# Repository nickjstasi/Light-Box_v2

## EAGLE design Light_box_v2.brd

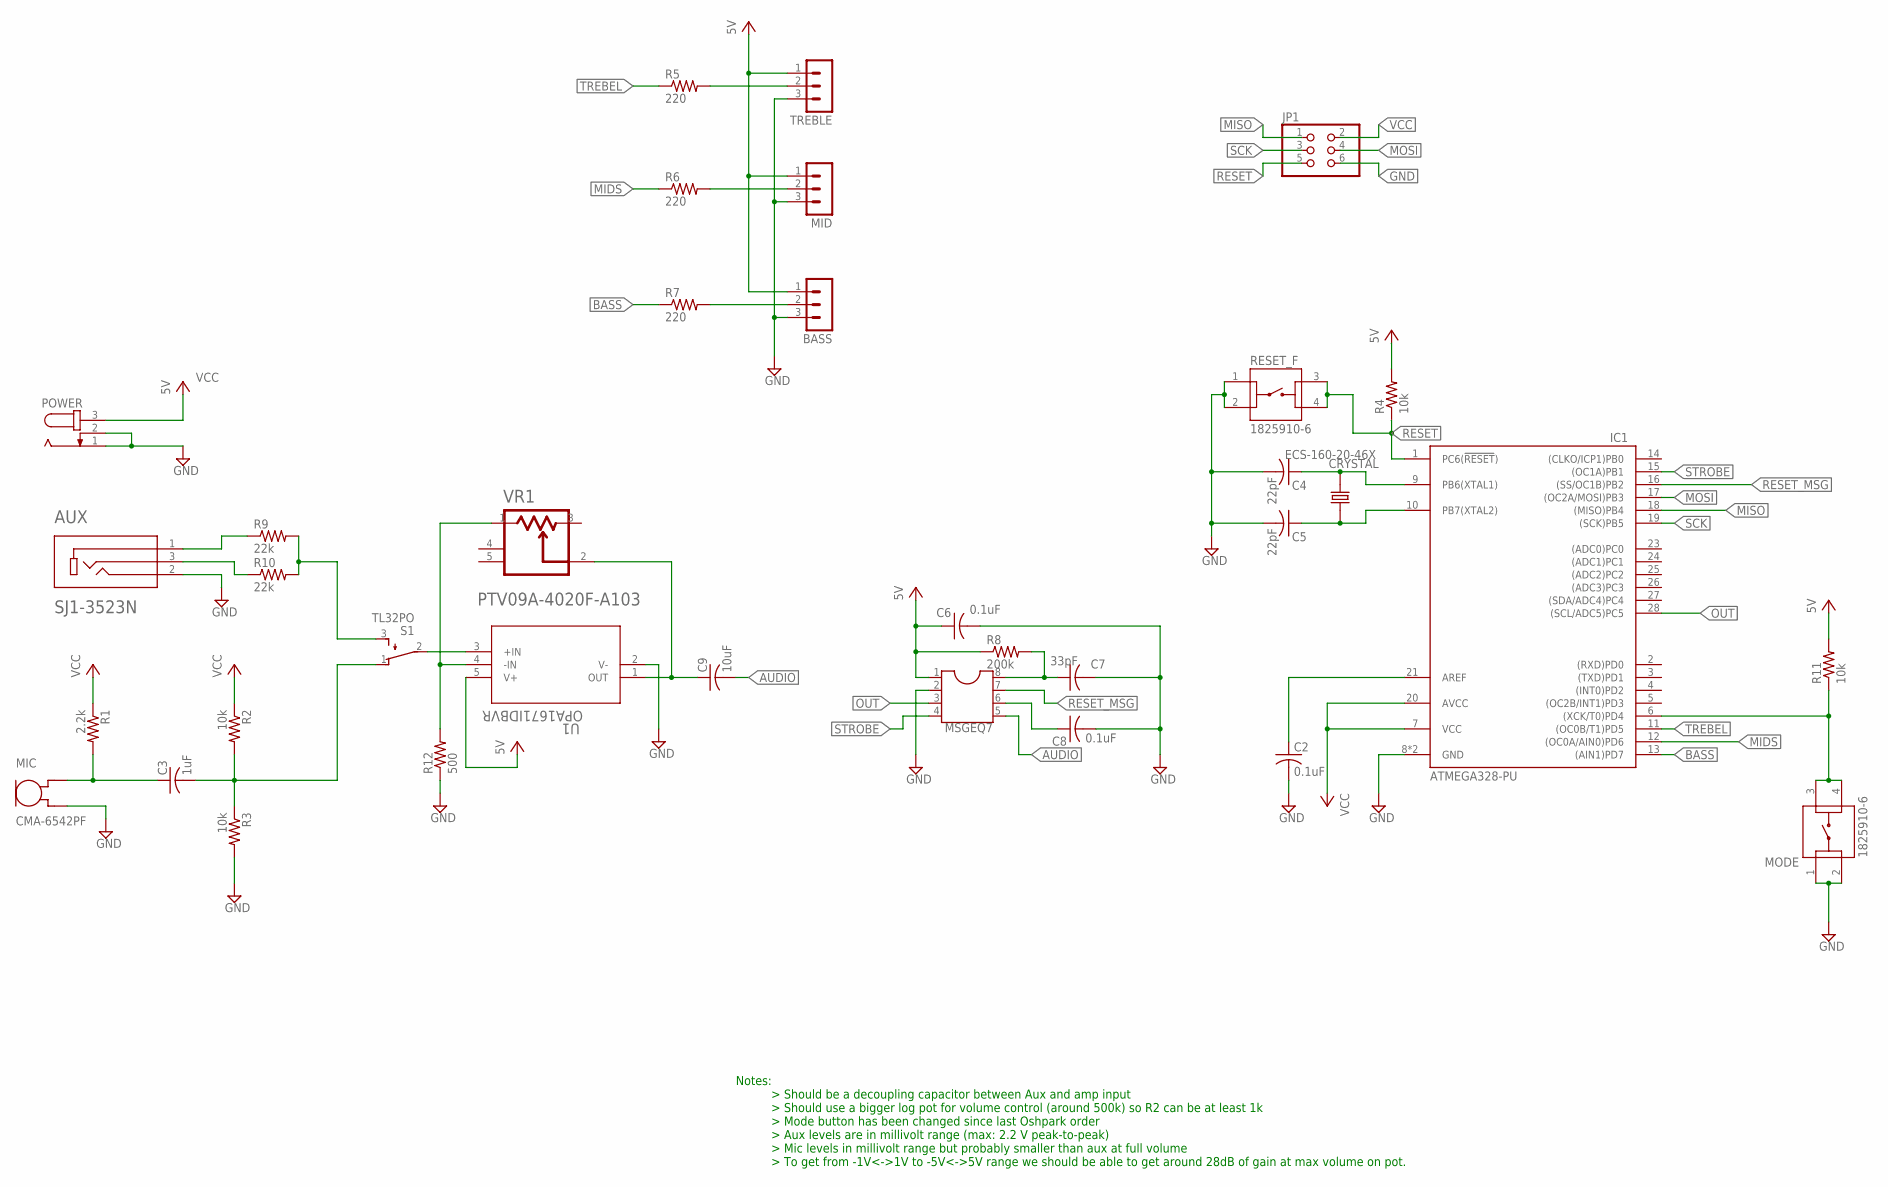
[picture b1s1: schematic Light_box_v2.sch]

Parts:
AUX: SJ1-3523N; CUI_SJ1-3523N
BASS: MA03-1
C2, C6, C8: 0.1uF; C0805
C3: 1uF; C0805
C4, C5: 22pF; C0805
C7: 33pF; C0805
C9: 10uF; C0805
CRYSTAL: ECS-160-20-46X; XTAL_ECS-160-20-46X
IC1: ATMEGA328-PU; DIL28
JP1: PINHD-2X3; 2X03
MIC: CMA-6542PF; CUI_CMA-6542PF
MID: MA03-1
MODE: 1825910-6; SW_1825910-6-4
MSGEQ7: DIL8; DIL08
POWER: JACK-PLUG1; SPC4078
R1: 2.2k; R0805
R2, R3, R4, R11: 10k; R0805
R5, R6, R7: 220; R0805
R8: 200k; R0805
R9, R10: 22k; R0805
R12: 500; R0805
RESET_F: 1825910-6; SW_1825910-6-4
S1: TL32PO; TL3XPO
TREBLE: MA03-1
U1: OPA1671IDBVR; SOT23-DBV5_TEX
VR1: BOURNS_PTV09A-4020F-A103BOURNS_PTV09A-4020F-A103_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; BOURNS_PTV09A-4020F-A103_0

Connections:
AUDIO: C9.2, MSGEQ7.5
BASS: IC1.13 ((AIN1)PD7), R7.1
GND: AUX.2, BASS.3, C2.2, C4.2, C5.2, C6.2, C7.2, C8.2, IC1.8 (GND), IC1.22 (GND), JP1.6, MIC.GND, MID.3, MODE.1, MODE.2, MSGEQ7.2, POWER.1, POWER.2, R3.2, R12.1, RESET_F.1, RESET_F.2, TREBLE.3, U1.2 (V-)
MIDS: IC1.12 ((OC0A/AIN0)PD6), R6.1
MISO: IC1.18 ((MISO)PB4), JP1.1
MOSI: IC1.17 ((OC2A/MOSI)PB3), JP1.4
unnamed: C3.1, MIC.OUT, R1.2
unnamed: C3.2, R2.2, R3.1, S1.1 (O)
unnamed: AUX.1, R9.1
unnamed: C4.1, CRYSTAL.2, IC1.9 (PB6(XTAL1))
unnamed: C5.1, CRYSTAL.1, IC1.10 (PB7(XTAL2))
unnamed: R5.2, TREBLE.2
unnamed: C9.1, U1.1 (OUT), VR1.2
unnamed: MID.2, R6.2
unnamed: BASS.2, R7.2
unnamed: C7.1, MSGEQ7.8, R8.2
unnamed: C8.1, MSGEQ7.6
unnamed: AUX.3, R10.1
unnamed: R12.2, U1.4 (-IN), VR1.1
unnamed: R9.2, R10.2, S1.3 (S)
unnamed: C2.1, IC1.21 (AREF)
unnamed: S1.2, U1.3 (+IN)
unnamed: IC1.6 ((XCK/T0)PD4), MODE.3, MODE.4, R11.1
OUT: IC1.28 ((SCL/ADC5)PC5), MSGEQ7.3
RESET: IC1.1 (PC6(!RESET!)), JP1.5, R4.1, RESET_F.3, RESET_F.4
RESET_MSG: IC1.16 ((SS/OC1B)PB2), MSGEQ7.7
SCK: IC1.19 ((SCK)PB5), JP1.3
STROBE: IC1.15 ((OC1A)PB1), MSGEQ7.4
TREBEL: IC1.11 ((OC0B/T1)PD5), R5.1
VCC: BASS.1, C6.1, IC1.7 (VCC), IC1.20 (AVCC), JP1.2, MID.1, MSGEQ7.1, POWER.3, R1.1, R2.1, R4.2, R8.1, R11.2, TREBLE.1, U1.5 (V+)

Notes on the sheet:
Notes: > Should be a decoupling capacitor between Aux and amp input > Should use a bigger log pot for volume control (around 500k) so R2 can be at least 1k > Mode button has been changed since last Oshpark order > Aux levels are in millivolt range (max: 2.2 V peak-to-peak) > Mic levels in millivolt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

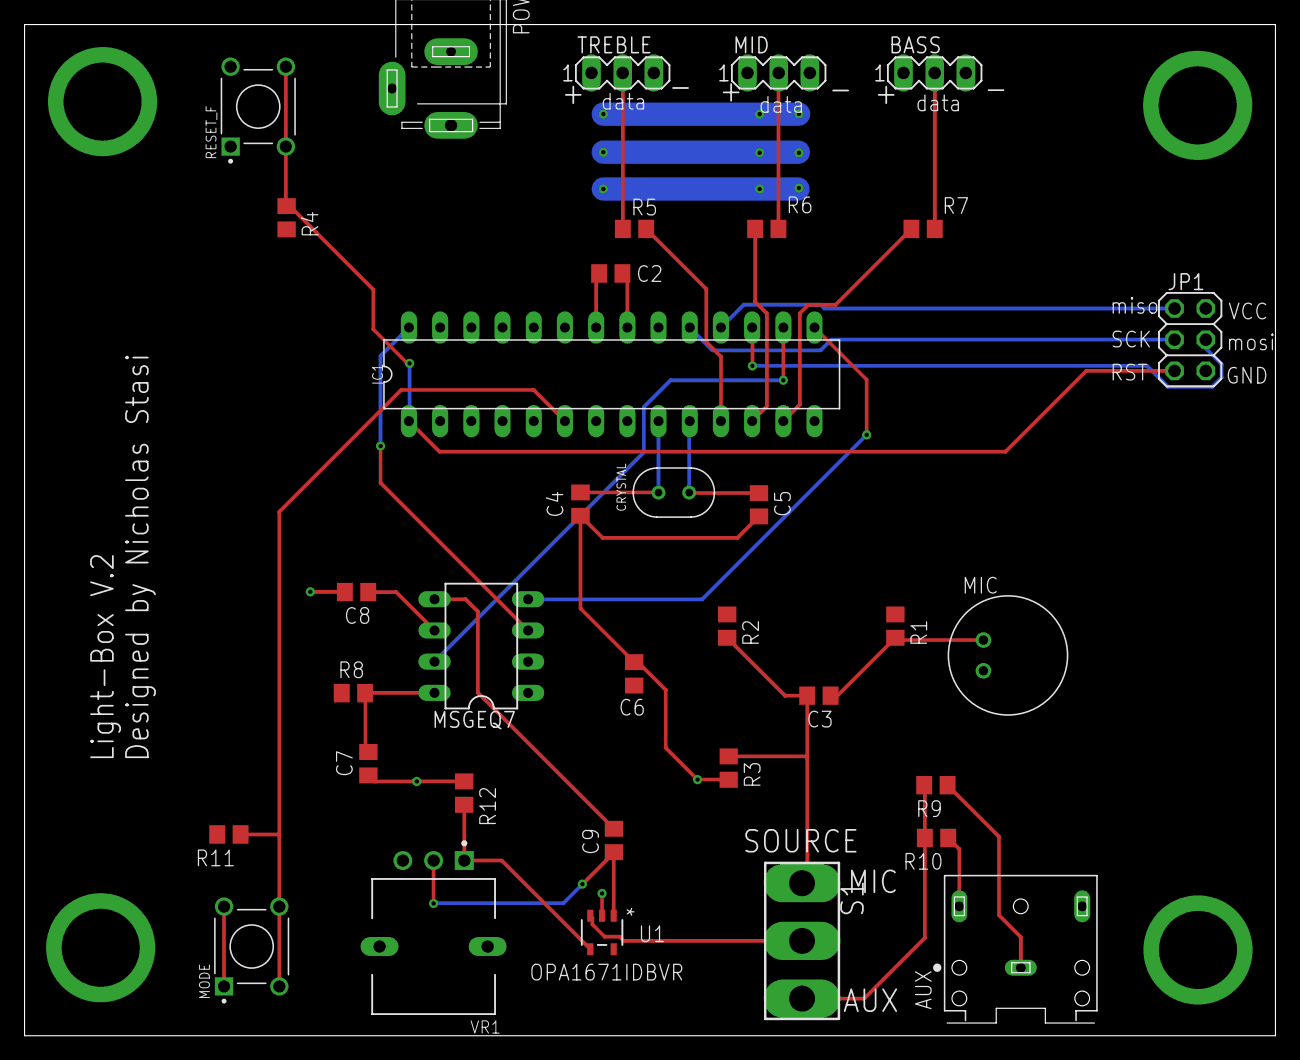
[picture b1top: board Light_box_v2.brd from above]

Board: 2 copper layers, 101.8 x 82.3 mm, 35 parts (0 on the bottom side), 30 nets.

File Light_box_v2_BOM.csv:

"Qty";"Value";"Device";"Package";"Parts";"Description";"BUILT_BY";"CENTROID_NOT_SPECIFIED";"COMMENT";"CONFIGURATION_POLE-THROW";"CONTACT_CURRENT_RATING";"COPYRIGHT";"CUI_PURCHASE_URL";"DATASHEET";"DESCRIPTION";"DIGI-KEY_PART_NUMBER";"DIGIKEY-PURCHASE-URL";"DIGIKEY_DESCRIPTION";"DIGIKEY_PART_NUMBER";"EU_ROHS_COMPLIANCE";"LEAD_FREE";"MANUFACTURER";"MANUFACTURER_PART_NUMBER";"MF";"MFG_PACKAGE_IDENT";"MOUSER-PURCHASE-URL";"MOUSER_PART_NUMBER";"MP";"MPN";"OC_FARNELL";"OC_NEWARK";"PACKAGE";"PARTREV";"POPULARITY";"POWER";"PREFIX";"RESISTANCE";"ROHS";"SOURCELIBRARY";"SPICEPREFIX";"STANDARD";"TEMPERATURE_RANGE_HIGH";"TEMPERATURE_RANGE_LOW";"VENDOR";
"1";"";"DIL8";"DIL08";"MSGEQ7";"Dual In Line / Socket";"";"";"";"";"";"";"";"";"";"";"";"";"";"";"";"";"";"";"";"";"";"";"";"";"";"";"";"8";"";"";"";"";"";"";"";"";"";"";
"1";"";"JACK-PLUG1";"SPC4078";"POWER";"DC POWER JACK";"";"";"";"";"";"";"";"";"";"";"";"";"";"";"";"";"";"";"";"";"";"";"";"unknown";"unknown";"";"";"3";"";"";"";"";"";"";"";"";"";"";
"3";"";"MA03-1";"MA03-1";"BASS, MID, TREBLE";"PIN HEADER";"";"";"";"";"";"";"";"";"";"";"";"";"";"";"";"";"";"";"";"";"";"";"";"unknown";"unknown";"";"";"48";"";"";"";"";"";"";"";"";"";"";
"1";"";"PINHD-2X3";"2X03";"JP1";"PIN HEADER";"";"";"";"";"";"";"";"";"";"";"";"";"";"";"";"";"";"";"";"";"";"";"";"";"";"";"";"62";"";"";"";"";"";"";"";"";"";"";
"3";"0.1uF";"C-USC0805";"C0805";"C2, C6, C8";"CAPACITOR, American symbol";"";"";"";"";"";"";"";"";"";"";"";"";"";"";"";"";"";"";"";"";"";"";"";"";"";"";"";"63";"";"";"";"";"";"C";"";"";"";"";
"4";"10k";"R-US_R0805";"R0805";"R2, R3, R4, R11";"RESISTOR, American symbol";"";"";"";"";"";"";"";"";"";"";"";"";"";"";"";"";"";"";"";"";"";"";"";"";"";"";"";"85";"";"";"";"";"";"R";"";"";"";"";
"1";"10uF";"C-USC0805";"C0805";"C9";"CAPACITOR, American symbol";"";"";"";"";"";"";"";"";"";"";"";"";"";"";"";"";"";"";"";"";"";"";"";"";"";"";"";"63";"";"";"";"";"";"C";"";"";"";"";
"2";"1825910-6";"1825910-6";"SW_1825910-6-4";"MODE, RESET_F";"Switch Tactile OFF (ON) SPST Round Button PC Pins 0.05A 24VDC 100000Cycles 1.57N Thru-Hole Loose";"";"";"1825910-6";"Single Pole - Single Throw";"50 mA";"";"";"";" Switch Push Button OFF (ON) SPST Round Button 0.05A 24VDC Momentary Contact PC Pins Thru-Hole ";"450-1650-ND";"https://snapeda.com/shop?store=DigiKey&id=424522";"";"";"Compliant";"";"";"";"TE Connectivity";"";"";"";"1825910-6";"";"";"";"None";"";"";"";"";"";"";"";"";"";"";"";"";
"1";"1uF";"C-USC0805";"C0805";"C3";"CAPACITOR, American symbol";"";"";"";"";"";"";"";"";"";"";"";"";"";"";"";"";"";"";"";"";"";"";"";"";"";"";"";"63";"";"";"";"";"";"C";"";"";"";"";
"1";"2.2k";"R-US_R0805";"R0805";"R1";"RESISTOR, American symbol";"";"";"";"";"";"";"";"";"";"";"";"";"";"";"";"";"";"";"";"";"";"";"";"";"";"";"";"85";"";"";"";"";"";"R";"";"";"";"";
"1";"200k";"R-US_R0805";"R0805";"R8";"RESISTOR, American symbol";"";"";"";"";"";"";"";"";"";"";"";"";"";"";"";"";"";"";"";"";"";"";"";"";"";"";"";"85";"";"";"";"";"";"R";"";"";"";"";
"3";"220";"R-US_R0805";"R0805";"R5, R6, R7";"RESISTOR, American symbol";"";"";"";"";"";"";"";"";"";"";"";"";"";"";"";"";"";"";"";"";"";"";"";"";"";"";"";"85";"";"";"";"";"";"R";"";"";"";"";
"2";"22k";"R-US_R0805";"R0805";"R9, R10";"RESISTOR, American symbol";"";"";"";"";"";"";"";"";"";"";"";"";"";"";"";"";"";"";"";"";"";"";"";"";"";"";"";"85";"";"";"";"";"";"R";"";"";"";"";
"2";"22pF";"C-USC0805";"C0805";"C4, C5";"CAPACITOR, American symbol";"";"";"";"";"";"";"";"";"";"";"";"";"";"";"";"";"";"";"";"";"";"";"";"";"";"";"";"63";"";"";"";"";"";"C";"";"";"";"";
"1";"33pF";"C-USC0805";"C0805";"C7";"CAPACITOR, American symbol";"";"";"";"";"";"";"";"";"";"";"";"";"";"";"";"";"";"";"";"";"";"";"";"";"";"";"";"63";"";"";"";"";"";"C";"";"";"";"";
"1";"500";"R-US_R0805";"R0805";"R12";"RESISTOR, American symbol";"";"";"";"";"";"";"";"";"";"";"";"";"";"";"";"";"";"";"";"";"";"";"";"";"";"";"";"85";"";"";"";"";"";"R";"";"";"";"";
"1";"ATMEGA328-PU";"ATMEGA328-PU";"DIL28";"IC1";"Atmel ATmega48/88/168/328 AVR Microcontroller";"";"";"";"";"";"";"";"";" IC MCU 8BIT 32KB FLASH 28DIP ";"";"https://snapeda.com/shop?store=DigiKey&id=4833845";"";"";"";"";"";"";"Microchip Technology";"";"https://snapeda.com/shop?store=Mouser&id=4833845";"";"ATMEGA328-PU";"";"";"";"None";"";"";"";"";"";"";"";"";"";"";"";"";
"1";"BOURNS_PTV09A-4020F-A103BOURNS_PTV09A-4020F-A103_0_0";"BOURNS_PTV09A-4020F-A103BOURNS_PTV09A-4020F-A103_0_0";"BOURNS_PTV09A-4020F-A103_0";"VR1";"PTV09 series 9mm Potentiometer";"";"No";"";"";"";"";"";"http://www.bourns.com/data/global/pdfs/PTV09.pdf";"";"";"";"RES POT 10K OHM 1/20W CARBON LOG";"PTV09A-4020F-A103-ND";"";"yes";"";"";"Bourns";"PTV09A-4";"";"652-PTV09A-4020FA103";"";"PTV09A-4020F-A103";"";"";"POT_PTH_9MMO";"";"";"50mW";"VR";"10k";"yes";"";"";"";"+50°C";"-10°C";"";
"1";"CMA-6542PF";"CMA-6542PF";"CUI_CMA-6542PF";"MIC";"9.7 mm, Omnidirectional, PCB Mount, 4.5 Vdc, Electret Condenser Microphone";"";"";"";"";"";"";"https://www.cuidevices.com/product/audio/microphones/electre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";"";"9.7 mm, Omnidirectional, PCB Mount, 4.5 Vdc, Electret Condenser Microphone";"102-1720-ND";"https://snapeda.com/shop?store=DigiKey&id=316835";"";"";"";"";"";"";"CUI Devices";"";"https://snapeda.com/shop?store=Mouser&id=316835";"";"CMA-6542PF";"";"";"";" CUI Inc.";"";"";"";"";"";"";"";"";"";"";"";"";
"1";"ECS-160-20-46X";"ECS-160-20-46X";"XTAL_ECS-160-20-46X";"CRYSTAL";"QUARTZ CRYSTAL  T/H";"";"";"";"";"";"";"";"";" 16MHz ±30ppm Crystal 20pF 50 Ohms HC-46/X ";"XC1759-ND";"https://snapeda.com/shop?store=DigiKey&id=628017";"";"";"";"";"";"";"ECS Inc.";"";"https://snapeda.com/shop?store=Mouser&id=628017";"";"ECS-160-20-46X";"";"";"";"HC46/X ECS International";"";"";"";"";"";"";"";"";"";"";"";"";
"1";"OPA1671IDBVR";"OPA1671IDBVR";"SOT23-DBV5_TEX";"U1";"";"EMA_Cory";"";"";"";"";"Copyright (C) 2018 Accelerated Designs. All rights reserved";"";"https://www.ti.com/lit/ds/symlink/opa1671.pdf";"";"";"";"";"";"";"";"";"OPA1671IDBVR";"";"";"";"";"";"";"";"";"";"";"";"";"";"";"";"TI_2020-03-25";"";"";"";"";"Texas Instruments";
"1";"SJ1-3523N";"SJ1-3523N";"CUI_SJ1-3523N";"AUX";"3.5 mm Right-Angle Stereo Jack, 3 Pin PCB Mount, Non-Threaded";"";"";"";"";"";"";"";"";"";"";"";"";"";"";"";"CUI";"";"";"";"";"";"";"";"";"";"";"1.02";"";"";"";"";"";"";"";"Manufacturer recommendation";"";"";"";
"1";"TL32PO";"TL32PO";"TL3XPO";"S1";"TINY SWITCH ON - MOM";"";"";"";"";"";"";"";"";"";"";"";"";"";"";"";"";"";"";"";"";"";"";"";"";"";"";"";"2";"";"";"";"";"";"";"";"";"";"";

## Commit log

2020-08-18 creating git repo for Light box project
2020-08-18 adding gitignore and pdf
2020-08-28 Adding some datasheets. Corrected error in mode button and added values to components
2020-08-28 Adding auto-generated BOM

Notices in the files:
parts and their libraries:
COPYRIGHT: Copyright (C) 2018 Accelerated Designs. All rights reserved
